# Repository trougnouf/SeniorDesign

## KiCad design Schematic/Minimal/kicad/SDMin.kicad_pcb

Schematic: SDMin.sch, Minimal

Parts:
BT1: Battery; 18650BatteryHolder
C1, C11: 10uF; C_Radial_D5_L11_P2.5
C2: 4.7uF; C_0805_HandSoldering
C3, C8: 1uF; C_Radial_D5_L11_P2.5
C4, C5, C9, C12, C14, C16, C19, C20, C21, C22, C23, C24, C25, C26, C31, C32, C33, C34: 0.1uF; C_0805_HandSoldering
C6, C10, C13, C15, C17: 4.7uF; C_Radial_D5_L11_P2.5
C7: 10uF; C_0805_HandSoldering
C18: 47uF; C_Radial_D5_L11_P2.5
C27: 470pF; C_0805_HandSoldering
C28: 4.7nF; C_0805_HandSoldering
C29, C30: 22pF; C_0805_HandSoldering
C35, C36, C37: C_Small
CON1: uSD_Card; MicroSD
D1: Led_Small; LED_0603
D2: Led_B; LED_0603
D3: Led_R; LED_0603
JP1, JP2: Jumper_NC_Small; Pin_Header_Straight_1x02
L1, L2: 4.7uH; Neosid_Inductor_SM-NE29_SMD1008
M1: LaserBracket; LaserHolder
P1: USB_B; USB_Micro-B
P2, P3, P4: CONN_01X04; Pin_Header_Straight_1x04
P5: CONN_01X02; Pin_Header_Straight_1x02
P6: CONN_01X02; Socket_Strip_Straight_1x02
R1, R2, R3, R4, R5, R6, R7, R8, R20: 10K; R_0805_HandSoldering
R9, R10, R11, R12, R13: 47K; R_0805_HandSoldering
R14, R15: 4.7; R_0805_HandSoldering
R16: 1k; R_0805_HandSoldering
R17: 1M; R_0805_HandSoldering
R18: 470; R_0805_HandSoldering
R19: 47; R_0805_HandSoldering
SW1, SW2, SW3, SW4, SW5, SW6, SW7, SW8, SW9: SW_PUSH; SW_PUSH_SMALL
U1: PAM2301; SOT-23-5
U2: XC9140; SOT-23-5
U3: MCP73811/2; SOT-23-5
U4: STM32L476R; LQFP-64_10x10mm_Pitch0.5mm
U5: Lightware_SF10/A; Socket_Strip_Straight_1x04_3467
U6: UART; Socket_Strip_Straight_1x02
U7: DebugPins; Socket_Strip_Straight_1x06
U8: MLX90393; QFN-16-1EP_3x3mm_Pitch0.5mm
U9: LS20031; LS20031+H
U10: ADMP401-BB; INMP401-bb
U11: RN-52
U12: STA013; SOIC-28_7.5x17.9mm_Pitch1.27mm
X1: 14.7456MHz; Crystal_HC49-SD_SMD

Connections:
+5V: JP1.2, U5.7 (V+)
+BATT: BT1.1, C1.1, C2.1, C8.1, L1.1, P5.2, U1.4 (VIN), U2.3 (Vbat), U3.3 (VBAT)
/3VEN: P5.1, U1.1 (EN)
/5VEN: U2.1 (CE), U4.38 (PC7)
/in1: R5.2, SW6.1, U4.41 (PA8)
/in2: R6.2, SW7.1, U4.43 (PA10)
/in3: R7.2, SW8.1, U4.44 (PA11)
/in4: R8.2, SW9.1, U4.45 (PA12)
/in5: R1.2, SW1.1, U4.3 (PC14-OSC32_IN)
/in6: R2.2, SW2.1, U4.4 (PC15-OSC32_OUT)
/in7: R3.2, SW3.1, U4.5 (PH0-OSC_IN)
/in8: R4.2, SW4.1, U4.6 (PH1-OSC_OUT)
NRST: R20.2, SW5.1, U4.7 (NRST), U7.4 (NRST)
unnamed: C3.2, P1.1 (VCC), U3.1 (CE), U3.4 (VDD), U3.5 (PROG)
unnamed: C7.1, JP1.1, U2.4 (Vout)
unnamed: C11.2, JP2.1, L2.2, U1.5 (VOUT/FB)
unnamed: C26.1, R15.2, U12.18 (PVSS)
unnamed: C26.2, R14.2, U12.17 (PVDD)
unnamed: C27.1, R16.1, U12.19 (FILT)
unnamed: C28.1, R16.2
unnamed: C29.1, R17.2, U12.20 (XTO), X1.1
unnamed: C30.1, R17.1, U12.21 (XTI), X1.2
unnamed: D1.2 (A), U4.61 (PB8)
unnamed: D2.1 (K), U11.33 (LED0)
unnamed: D2.2 (A), R19.2
unnamed: D3.1 (K), U11.32 (LED1)
unnamed: D3.2 (A), R18.2
unnamed: L1.2, U2.5 (Lx)
unnamed: L2.1, U1.3 (SW)
unnamed: P3.1, U11.26 (PCM_CLK)
unnamed: P3.2, U11.25 (PCM_SYNC)
unnamed: P3.3, U11.24 (PCM_OUT)
unnamed: P3.4, U11.23 (PCM_IN)
unnamed: P4.1, U12.10 (SCKT)
unnamed: P4.2, U12.11 (LRCKT)
unnamed: P4.4, U12.9 (SDO)
PA0_las: U4.14 (PA0), U5.4 (RXD)
PA1_las: U4.15 (PA1), U5.3 (TXD)
PA2_UART: U4.16 (PA2), U6.2 (RX)
PA3_UART: U4.17 (PA3), U6.1 (TX)
PA4_BTpcm-Sync: P2.2, U4.20 (PA4)
PA5_MP3-SCK: U4.21 (PA5), U12.6 (SCKR)
PA6_BT-RTS: U4.22 (PA6), U11.14 (UART_RTS)
PA7_MP3-SDI: U4.23 (PA7), U12.5 (SDI)
PA9_GPS-RX: U4.42 (PA9), U9.2 (RX)
PA13_dbg: U4.46 (PA13), U7.2 (PA13)
PA14_dbg: U4.49 (PA14), U7.1 (PA14)
PA15_SD-DET: CON1.9 (CARD_DETECT), U4.50 (PA15)
PB0_mic: U4.26 (PB0), U10.1 (AUD)
PB1_BT-CTS: U4.27 (PB1), U11.15 (UART_CTS)
PB2_BT-GP2: U4.28 (PB2), U11.2 (GPIO3)
PB3_BTpcm-CLK: P2.1, U4.55 (PB3)
PB5_BTpcm-IN: P2.4, U4.57 (PB5)
PB7_GPS-TX: U4.59 (PB7), U9.3 (TX)
PB9_MAG-CS: U4.62 (PB9), U8.2 (SENB/CS)
PB10_MAG-SPC: U4.29 (PB10), U8.3 (SCL/SCLK)
PB11_BT-GP9: U4.30 (PB11), U11.11 (GPIO9)
PB12_MAG-INT: U4.33 (PB12), U8.1 (INT)
PB13_MAG-TRIG: U4.34 (PB13), U8.7 (INT/TRIG)
PB14_MP3-RST: U4.35 (PB14), U12.26 (~RESET)
PB15_MAG-MOSI: U4.36 (PB15), U8.5 (SDA/MOSI)
PC0_MP3-SCL: U4.8 (PC0), U12.4 (SCL)
PC1_MP3-SDA: U4.9 (PC1), U12.3 (SDA)
PC2_MAG-MISO: U4.10 (PC2), U8.6 (MISO)
PC4_BT-RX: U4.24 (PC4), U11.17 (UART_RX)
PC5_BT-TX: U4.25 (PC5), U11.16 (UART_TX)
PC6_MP3-DR: U4.37 (PC6), U12.28 (DATA_REQ)
PC8_SD-D0: CON1.7 (DAT0), R10.1, U4.39 (PC8)
PC9_SD-D1: CON1.8 (DAT1), R9.1, U4.40 (PC9)
PC10_SD-D2: CON1.1 (DAT2), R13.2, U4.51 (PC10)
PC11_SD-D3: CON1.2 (CD/DAT3), R12.2, U4.52 (PC11)
PC12_SD-CK: CON1.5 (CLK), U4.53 (PC12)
PC13_dbg: U4.2 (PC13), U7.3 (PC13)
PD2_SD-CMD: CON1.3 (CMD), R11.1, U4.54 (PD2)
x-in-1: P6.2, U4.56 (PB4)
x-in-2: P6.1, U4.58 (PB6)

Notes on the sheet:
Power subsystem
Compass
MCU
SD card
debug/program headers
Laser headers
UART headers
GPS
Audio subsystem
Microphone breakout board
Bluetooth
MP3 codec
USB
Charger
3.3V
misc

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
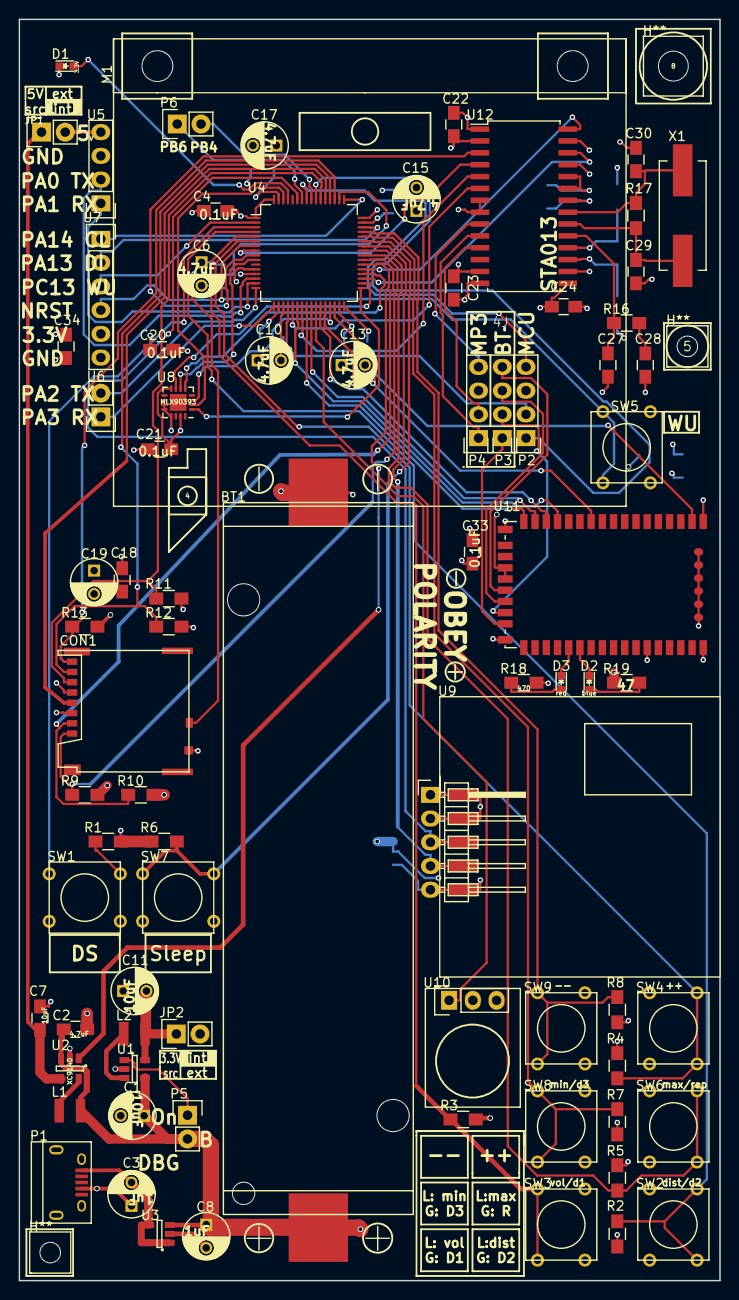
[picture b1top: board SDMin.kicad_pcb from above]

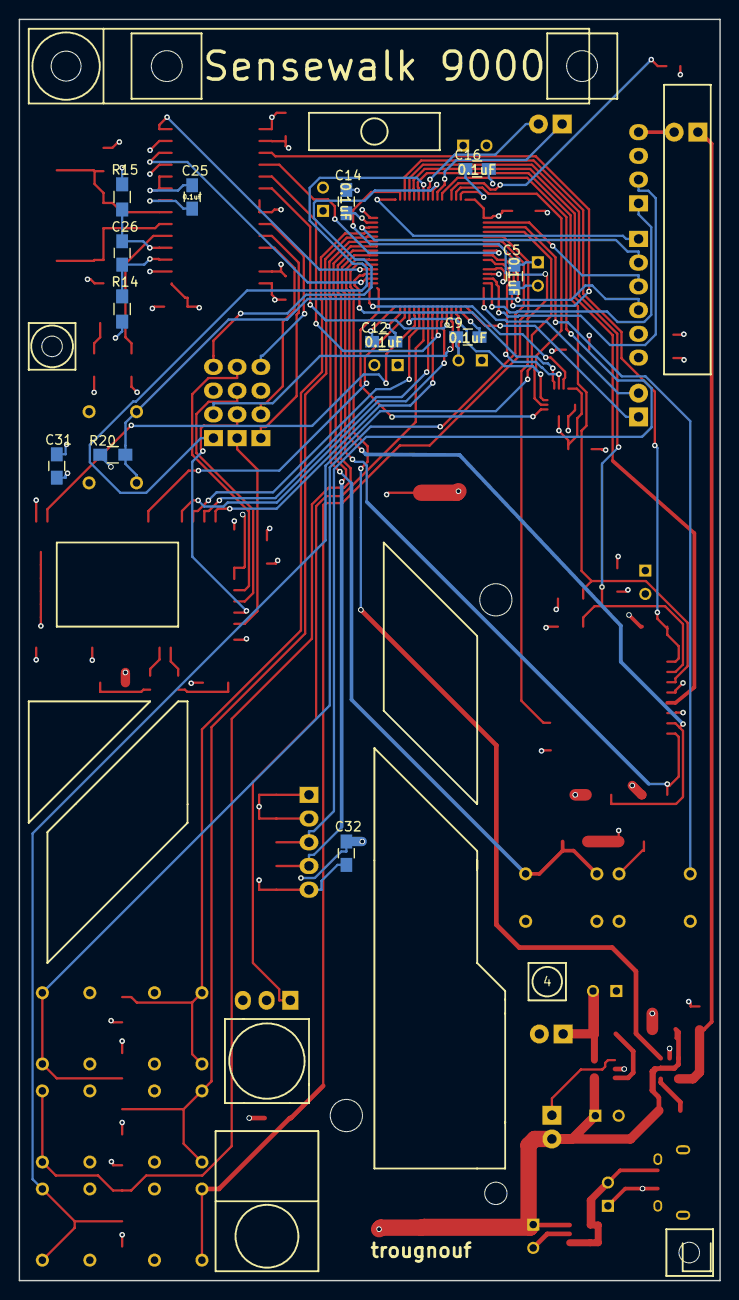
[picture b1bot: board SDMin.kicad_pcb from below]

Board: 4 copper layers, 75.0 x 135.0 mm, 95 parts (12 on the bottom side), 78 nets.

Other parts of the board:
H**: H2.2; mountinghole2.2
H**#2: 3.2H; mountinghole3.2
H**#3: H2.2; mountinghole2.2

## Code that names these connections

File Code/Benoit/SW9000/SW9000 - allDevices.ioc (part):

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Mcu.Name=STM32L476R(C-E-G)Tx
Mcu.Package=LQFP64
Mcu.UserName=STM32L476RETx
PA0.GPIOParameters=GPIO_Label
PA0.GPIO_Label=UART4_TX_Laser
PA0.Mode=Asynchronous
PA0.Signal=UART4_TX
PA1.GPIOParameters=GPIO_Label
PA1.GPIO_Label=UART4_RX_Laser
PA1.Mode=Asynchronous
PA1.Signal=UART4_RX
PA10.Signal=GPIO_Input
PA11.Signal=GPIO_Input
PA12.Signal=GPIO_Input
PA13.Mode=Serial-Wire
PA13.Signal=SYS_JTMS-SWDIO
PA14.Mode=Serial-Wire
PA14.Signal=SYS_JTCK-SWCLK
PA15.GPIOParameters=GPIO_Label
PA15.GPIO_Label=SDMMC1_Detect
PA15.Signal=GPIO_Input
PA2.GPIOParameters=GPIO_Label
PA2.GPIO_Label=USART2_TX_PC
PA2.Mode=Asynchronous
PA2.Signal=USART2_TX
PA3.GPIOParameters=GPIO_Label
PA3.GPIO_Label=USART2_RX_PC
PA3.Mode=Asynchronous
PA3.Signal=USART2_RX
PA4.Mode=SAI_B_Master
PA4.Signal=SAI1_FS_B
PA5.GPIOParameters=GPIO_Label
PA5.GPIO_Label=SPI1_SCK_Codec
PA5.Mode=TX_Only_Simplex_Unidirect_Master
PA5.Signal=SPI1_SCK
PA6.GPIOParameters=GPIO_Label
PA6.GPIO_Label=USART3_CTS_BT
PA6.Mode=CTS_RTS
PA6.Signal=USART3_CTS
PA7.GPIOParameters=GPIO_Label
PA7.GPIO_Label=SPI1_MOSI_Codec
PA7.Mode=TX_Only_Simplex_Unidirect_Master
PA7.Signal=SPI1_MOSI
PA8.Signal=GPIO_Input
PA9.GPIOParameters=GPIO_Label
PA9.GPIO_Label=USART1_TX_GPS
PA9.Mode=Asynchronous
PA9.Signal=USART1_TX
PB0.GPIOParameters=GPIO_Label
PB0.GPIO_Label=VIBRATOR
PB0.Signal=GPIO_Output
PB1.GPIOParameters=GPIO_Label
PB1.GPIO_Label=USART3_RTS_BT
PB1.Mode=CTS_RTS
PB1.Signal=USART3_RTS
PB10.GPIOParameters=GPIO_Label
PB10.GPIO_Label=SPI2_SCK_Compass
PB10.Mode=Full_Duplex_Master
PB10.Signal=SPI2_SCK
PB11.GPIOParameters=GPIO_Label
PB11.GPIO_Label=BT_GP9
PB11.Signal=GPIO_Output
PB12.GPIOParameters=GPIO_Label
PB12.GPIO_Label=COMP_INT
PB12.Signal=GPIO_Input
PB13.GPIOParameters=GPIO_Label
PB13.GPIO_Label=INT2_Compass
PB13.Signal=GPIO_Input
PB14.GPIOParameters=GPIO_Label
PB14.GPIO_Label=RST_Codec
PB14.Signal=GPIO_Output
PB15.GPIOParameters=GPIO_Label
PB15.GPIO_Label=SPI2_MOSI_Compass
PB15.Mode=Full_Duplex_Master
PB15.Signal=SPI2_MOSI
PB2.GPIOParameters=GPIO_Label
PB2.GPIO_Label=BT_GP2
PB2.Signal=GPIO_Output
PB3.Mode=SAI_B_Master
PB3.Signal=SAI1_SCK_B
PB5.Mode=SAI_B_Master
PB5.Signal=SAI1_SD_B
PB7.GPIOParameters=GPIO_Label
PB7.GPIO_Label=USART1_RX_GPS
PB7.Mode=Asynchronous
PB7.Signal=USART1_RX
PB8.GPIOParameters=GPIO_Label
PB8.GPIO_Label=LED
PB8.Signal=GPIO_Output
PB9.GPIOParameters=GPIO_Label
PB9.GPIO_Label=COMP_CS
PB9.Signal=GPIO_Output
PC0.GPIOParameters=GPIO_Label
PC0.GPIO_Label=I2C3_SCL_Codec
PC0.Mode=I2C
PC0.Signal=I2C3_SCL
PC1.GPIOParameters=GPIO_Label
PC1.GPIO_Label=I2C3_SDA_Codec
PC1.Mode=I2C
PC1.Signal=I2C3_SDA
PC12.Mode=SD_1_bit
PC12.Signal=SDMMC1_CK
PC13.Mode=SYS-WakeUp2
PC13.Signal=SYS_WKUP2
PC14/OSC32_IN.Signal=GPIO_Input
PC15/OSC32_OUT.Signal=GPIO_Input
PC2.GPIOParameters=GPIO_Label
PC2.GPIO_Label=SPI2_MISO_Compass
PC2.Mode=Full_Duplex_Master
PC2.Signal=SPI2_MISO
PC4.GPIOParameters=GPIO_Label
PC4.GPIO_Label=USART3_TX_BT
PC4.Mode=Asynchronous
PC4.Signal=USART3_TX
PC5.GPIOParameters=GPIO_Label
PC5.GPIO_Label=USART3_RX_BT
PC5.Mode=Asynchronous
PC5.Signal=USART3_RX
PC6.GPIOParameters=GPIO_Label
PC6.GPIO_Label=Codec_DR
PC6.Signal=GPIO_Input
PC7.GPIOParameters=GPIO_Label
PC7.GPIO_Label=FIVEVOLTSEN
PC7.Signal=GPIO_Output
PC8.Mode=SD_1_bit
PC8.Signal=SDMMC1_D0
PD2.Mode=SD_1_bit
PD2.Signal=SDMMC1_CMD
PH0/OSC_IN.Signal=GPIO_Input
PH1/OSC_OUT.Signal=GPIO_Input
RCC.HSE_VALUE=8000000
RCC.SYSCLKFreq_VALUE=80000000
RCC.SYSCLKSource=RCC_SYSCLKSOURCE_PLLCLK
board=SW9000
boardIOC=true

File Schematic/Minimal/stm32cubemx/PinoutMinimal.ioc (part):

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Mcu.Name=STM32L476R(C-E-G)Tx
Mcu.Package=LQFP64
Mcu.UserName=STM32L476RETx
PA0.GPIOParameters=GPIO_Label
PA0.GPIO_Label=UART4_TX_Laser
PA0.Mode=Asynchronous
PA0.Signal=UART4_TX
PA1.GPIOParameters=GPIO_Label
PA1.GPIO_Label=UART4_RX_Laser
PA1.Mode=Asynchronous
PA1.Signal=UART4_RX
PA10.Signal=GPIO_Input
PA11.Signal=GPIO_Input
PA12.Signal=GPIO_Input
PA13.Mode=Serial-Wire
PA13.Signal=SYS_JTMS-SWDIO
PA14.Mode=Serial-Wire
PA14.Signal=SYS_JTCK-SWCLK
PA15.GPIOParameters=GPIO_Label
PA15.GPIO_Label=SDMMC1_Detect
PA15.Signal=GPIO_Input
PA2.GPIOParameters=GPIO_Label
PA2.GPIO_Label=USART2_TX_PC
PA2.Mode=Asynchronous
PA2.Signal=USART2_TX
PA3.GPIOParameters=GPIO_Label
PA3.GPIO_Label=USART2_RX_PC
PA3.Mode=Asynchronous
PA3.Signal=USART2_RX
PA4.Mode=SAI_B_Master
PA4.Signal=SAI1_FS_B
PA5.GPIOParameters=GPIO_Label
PA5.GPIO_Label=SPI1_SCK_Codec
PA5.Mode=TX_Only_Simplex_Unidirect_Master
PA5.Signal=SPI1_SCK
PA6.GPIOParameters=GPIO_Label
PA6.GPIO_Label=USART3_CTS_BT
PA6.Mode=CTS_RTS
PA6.Signal=USART3_CTS
PA7.GPIOParameters=GPIO_Label
PA7.GPIO_Label=SPI1_MOSI_Codec
PA7.Mode=TX_Only_Simplex_Unidirect_Master
PA7.Signal=SPI1_MOSI
PA8.Signal=GPIO_Input
PA9.GPIOParameters=GPIO_Label
PA9.GPIO_Label=USART1_TX_GPS
PA9.Mode=Asynchronous
PA9.Signal=USART1_TX
PB0.Signal=GPIO_Output
PB1.GPIOParameters=GPIO_Label
PB1.GPIO_Label=USART3_RTS_BT
PB1.Mode=CTS_RTS
PB1.Signal=USART3_RTS
PB10.GPIOParameters=GPIO_Label
PB10.GPIO_Label=SPI2_SCK_Compass
PB10.Mode=Full_Duplex_Master
PB10.Signal=SPI2_SCK
PB11.Signal=GPXTI11
PB12.GPIOParameters=GPIO_Label
PB12.GPIO_Label=INT1_Compass
PB12.Signal=GPIO_Input
PB13.GPIOParameters=GPIO_Label
PB13.GPIO_Label=INT2_Compass
PB13.Signal=GPIO_Input
PB14.GPIOParameters=GPIO_Label
PB14.GPIO_Label=RST_Codec
PB14.Signal=GPIO_Output
PB15.GPIOParameters=GPIO_Label
PB15.GPIO_Label=SPI2_MOSI_Compass
PB15.Mode=Full_Duplex_Master
PB15.Signal=SPI2_MOSI
PB3.Mode=SAI_B_Master
PB3.Signal=SAI1_SCK_B
PB5.Mode=SAI_B_Master
PB5.Signal=SAI1_SD_B
PB7.GPIOParameters=GPIO_Label
PB7.GPIO_Label=USART1_RX_GPS
PB7.Mode=Asynchronous
PB7.Signal=USART1_RX
PB9.GPIOParameters=GPIO_Label
PB9.GPIO_Label=SPI2_CS_Compass
PB9.Mode=NSS_Signal_Hard_Output
PB9.Signal=SPI2_NSS
PC0.GPIOParameters=GPIO_Label
PC0.GPIO_Label=I2C3_SCL_Codec
PC0.Mode=I2C
PC0.Signal=I2C3_SCL
PC1.GPIOParameters=GPIO_Label
PC1.GPIO_Label=I2C3_SDA_Codec
PC1.Mode=I2C
PC1.Signal=I2C3_SDA
PC10.Mode=SD_4_bits_Wide_bus
PC10.Signal=SDMMC1_D2
PC11.Mode=SD_4_bits_Wide_bus
PC11.Signal=SDMMC1_D3
PC12.Mode=SD_4_bits_Wide_bus
PC12.Signal=SDMMC1_CK
PC13.Mode=SYS-WakeUp2
PC13.Signal=SYS_WKUP2
PC14/OSC32_IN.Signal=GPIO_Input
PC15/OSC32_OUT.Signal=GPIO_Input
PC2.GPIOParameters=GPIO_Label
PC2.GPIO_Label=SPI2_MISO_Compass
PC2.Mode=Full_Duplex_Master
PC2.Signal=SPI2_MISO
PC3.GPIOParameters=GPIO_Label
PC3.GPIO_Label=ADC2_IN4_Mic
PC3.Signal=ADCx_IN4
PC4.GPIOParameters=GPIO_Label
PC4.GPIO_Label=USART3_TX_BT
PC4.Mode=Asynchronous
PC4.Signal=USART3_TX
PC5.GPIOParameters=GPIO_Label
PC5.GPIO_Label=USART3_RX_BT
PC5.Mode=Asynchronous
PC5.Signal=USART3_RX
PC8.Mode=SD_4_bits_Wide_bus
PC8.Signal=SDMMC1_D0
PC9.Mode=SD_4_bits_Wide_bus
PC9.Signal=SDMMC1_D1
PD2.Mode=SD_4_bits_Wide_bus
PD2.Signal=SDMMC1_CMD
PH0/OSC_IN.Signal=GPIO_Input
PH1/OSC_OUT.Signal=GPIO_Input
RCC.HSE_VALUE=8000000
RCC.SYSCLKFreq_VALUE=80000000
RCC.SYSCLKSource=RCC_SYSCLKSOURCE_PLLCLK
board=PinoutMinimal

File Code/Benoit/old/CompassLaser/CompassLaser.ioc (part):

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Mcu.Name=STM32F070RBTx
Mcu.Package=LQFP64
Mcu.UserName=STM32F070RBTx
PA1.GPIOParameters=GPIO_Label
PA1.GPIO_Label=INT
PA1.Signal=GPIO_Input
PA10.Mode=Asynchronous
PA10.Signal=USART1_RX
PA13.GPIOParameters=GPIO_Label
PA13.GPIO_Label=TMS
PA13.Mode=Serial-WireDebug
PA13.Signal=SYS_SWDIO
PA14.GPIOParameters=GPIO_Label
PA14.GPIO_Label=TCK
PA14.Mode=Serial-WireDebug
PA14.Signal=SYS_SWCLK
PA2.GPIOParameters=GPIO_Label
PA2.GPIO_Label=USART_TX
PA2.Mode=Asynchronous
PA2.Signal=USART2_TX
PA3.GPIOParameters=GPIO_Label
PA3.GPIO_Label=USART_RX
PA3.Mode=Asynchronous
PA3.Signal=USART2_RX
PA4.Signal=GPIO_Output
PA5.GPIOParameters=GPIO_Label
PA5.GPIO_Label=LD2 [Green Led]
PA5.Signal=GPIO_Output
PA6.Mode=Full_Duplex_Master
PA6.Signal=SPI1_MISO
PA7.Mode=Full_Duplex_Master
PA7.Signal=SPI1_MOSI
PA8.GPIOParameters=GPIO_Label
PA8.GPIO_Label=LED11
PA8.Signal=GPIO_Output
PA9.Mode=Asynchronous
PA9.Signal=USART1_TX
PB10.GPIOParameters=GPIO_Label
PB10.GPIO_Label=LED10
PB10.Signal=GPIO_Output
PB3.Mode=Full_Duplex_Master
PB3.Signal=SPI1_SCK
PB4.GPIOParameters=GPIO_Label
PB4.GPIO_Label=LED01
PB4.Signal=GPIO_Output
PB5.GPIOParameters=GPIO_Label
PB5.GPIO_Label=LED00
PB5.Signal=GPIO_Output
PB6.GPIOParameters=GPIO_Label
PB6.GPIO_Label=LED21
PB6.Signal=GPIO_Output
PC13.GPIOParameters=GPIO_Label,GPIO_ModeDefaultEXTI
PC13.GPIO_Label=B1 [Blue PushButton]
PC13.GPIO_ModeDefaultEXTI=GPIO_MODE_EVT_RISING
PC13.Signal=GPXTI13
PC7.GPIOParameters=GPIO_Label
PC7.GPIO_Label=LED20
PC7.Signal=GPIO_Output
PC9.GPIOParameters=GPIO_Label
PC9.GPIO_Label=TRIG
PC9.Signal=GPIO_Output
RCC.SYSCLKFreq_VALUE=48000000
RCC.SYSCLKSource=RCC_SYSCLKSOURCE_PLLCLK
board=NUCLEO-F070RB
boardIOC=true

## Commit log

2015-12-25 Initial commit. Datasheets and initial code w/RTOS example
2015-12-26 Added some datasheets
2015-12-26 Added STM32F7Cube firmware
2016-01-03 Added TODO list
2016-01-15 Added some documentation
2016-01-15 Uploaded datasheet for bluetooth and codec, started pinout
2016-01-16 List of passive components required for the MP3 decoder.
2016-01-21 Update TODO
2016-01-22 Added readme.txt containing useful functions/examples
2016-01-22 Add Pinout.ioc (STM32CubeMX), update Pinout.txt
2016-01-22 Update pinout
2016-01-22 Add STLink/Discovery built-in UART ports
2016-01-29 GPS data output
2016-01-30 sync, no progress
2016-01-31 Add FatFS support (SD card, text file)
2016-01-31 Laser(UART)-Nucleo pinout, initial struggle
2016-02-05 Getting one clean reading from the laser.
2016-02-05 Getting multiple readings from the laser.
2016-02-05 Copied laser code
2016-02-05 Working laser w/function calls. Needs speedup.
2016-02-05 Finished laser
2016-02-06 sync (starting Code/main/)
2016-02-06 Begin work on F030 bareboard
2016-02-07 Sync - worked on bare MCU
2016-02-07 Clean up directories
2016-02-07 Add Ross' schematic
2016-02-07 Add PinoutMinimal (done)
2016-02-08 Add STM32L476RET schematic, clean-up folders
2016-02-08 Work on minimal schematic, add power components
2016-02-09 Add schematic for the power subsystem, create all missing components
2016-02-11 Add Digikey invoices
2016-02-12 Add images used in the presentation
2016-02-12 Add presentation images, finish draft
2016-02-13 Add Codec, Bluetooth, debug to minimal schematic
2016-02-17 Add schematic (schematic done, need to draw footprints and design PCB layout)
2016-02-17 Add push buttons and battery switch to schematic
2016-02-17 Add HW footprints info, minor schematic change (mic)
2016-02-18 Update schematic (add software audio capability, prettier)
2016-02-18 Rename folder: schema->pdf
2016-02-19 sync (minor schematic change)
2016-02-19 Assign some footprints to schematic
2016-02-20 Update schematic, change compass (LGA->QFN)
2016-02-20 Update schematic, order capacitors/resistors/headers and list their size in HW
2016-02-21 Finish schematic, finish drawing footprints, associate all parts to footprints, get a reading from the GPS.
2016-02-22 Working on the PCB (third attempt). Misc schematic fixes (charger always on)
2016-02-22 Slight progress on PCB attempt 3
2016-02-23 PCB3 progress: Needs capacitors/resistors and push buttons
2016-02-23 Progressing on the PCB. Completed pinout for the standard board.
2016-02-23 Organize folders
2016-02-24 Working on PCB#4, now with FreeRouting
2016-02-25 Lots of progress on the mPCB
2016-02-26 PCB4-23
2016-02-26 PCB4:25
2016-02-26 PCB svg render
2016-02-29 Ordered PCB. Making no progress on the compass.
2016-02-29 Bedsync. Compass: applied a NSS/CS fix found on a forum, still no progress.
2016-02-29 Update standard board pinout
2016-03-04 Compass (desperate times): crap is about to get deleted
2016-03-04 Compass: killing it.
2016-03-09 sync (compass data)
2016-03-09 sync: trying to translate the magnet readings
2016-03-19 Compass works, pulling valid data.
2016-03-21 Compass appears to be flawless
2016-04-08 SW9000 on IAR
2016-04-13 Merging the things (Desktop)
2016-04-16 Laser cutter cad file for Sensewalk 9000
2016-04-16 Sensewalk 9000 development, worked on the GPS with Diego
2016-04-16 Sensewalk 9000 development (vibrator, laser, sd), worked on GPS with Diego
2016-04-17 Started work on compass w/ vibration and interrupt, starting STM32F7 board
2016-04-17 sync, SW9000->SW2
2016-04-19 Add presentation and Ross' board
2016-04-22 Code that was presented
2016-04-27 GPS: About to remove RTOS
2016-04-29 Fixed GPS code for Diego to graduate
2016-04-29 Organize files
2016-04-30 Modify final paper
2016-05-02 Add final documentation
